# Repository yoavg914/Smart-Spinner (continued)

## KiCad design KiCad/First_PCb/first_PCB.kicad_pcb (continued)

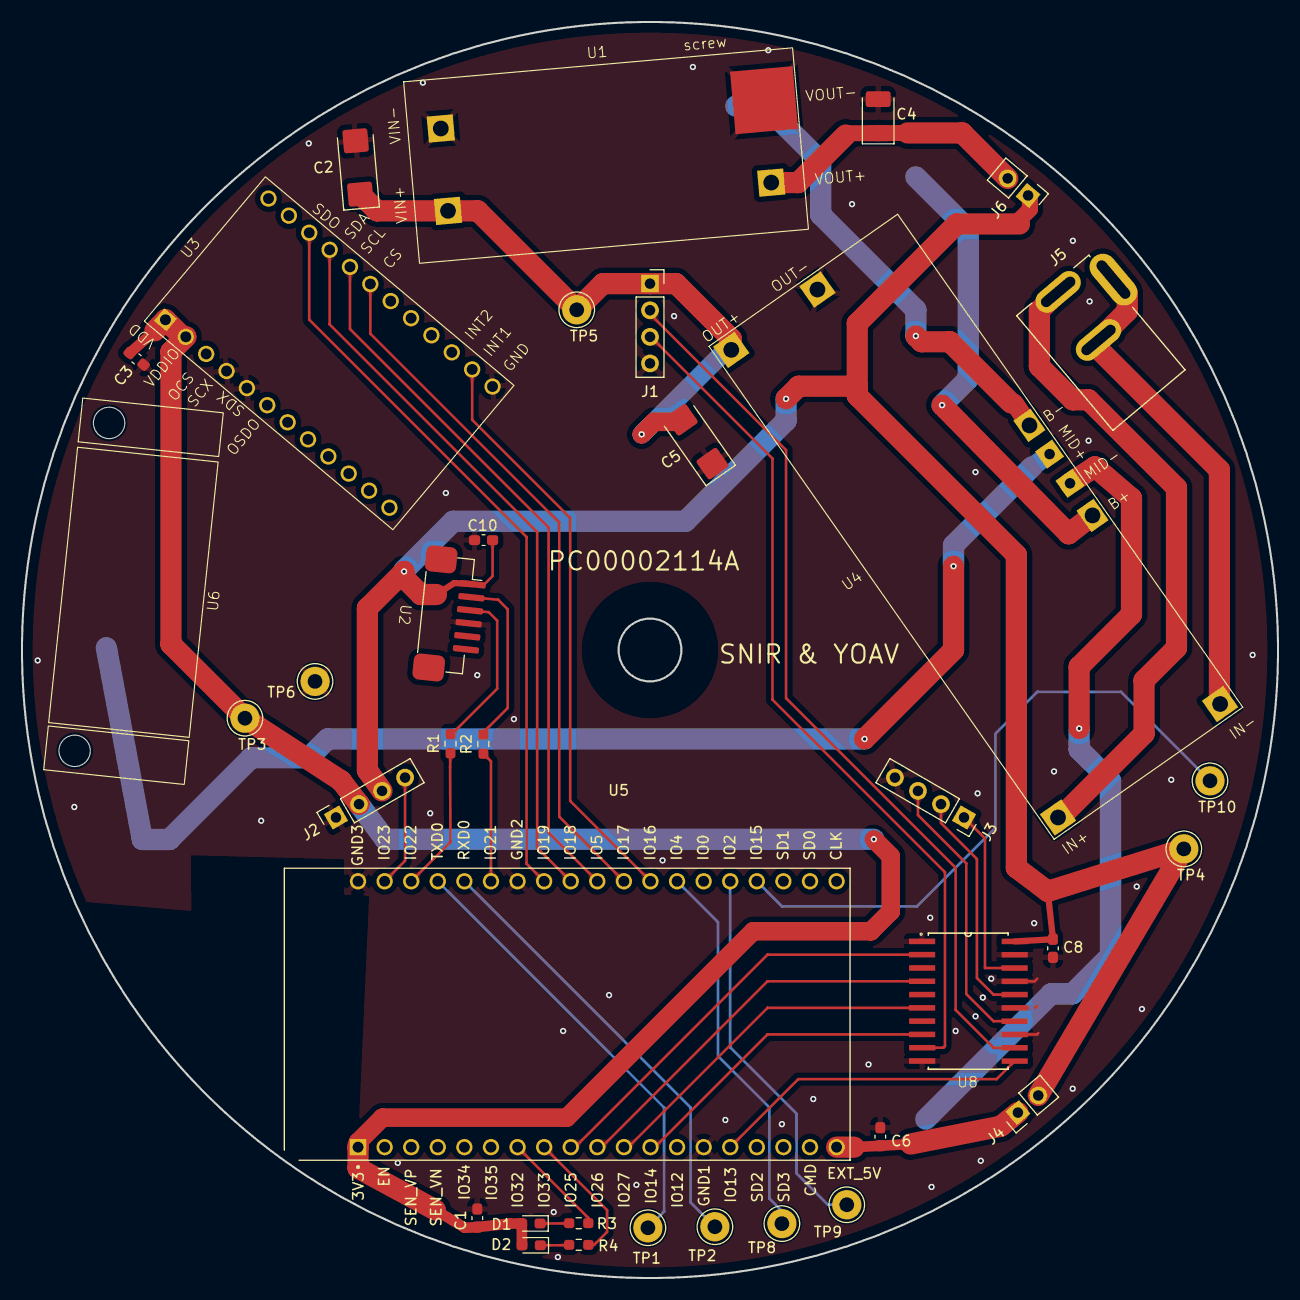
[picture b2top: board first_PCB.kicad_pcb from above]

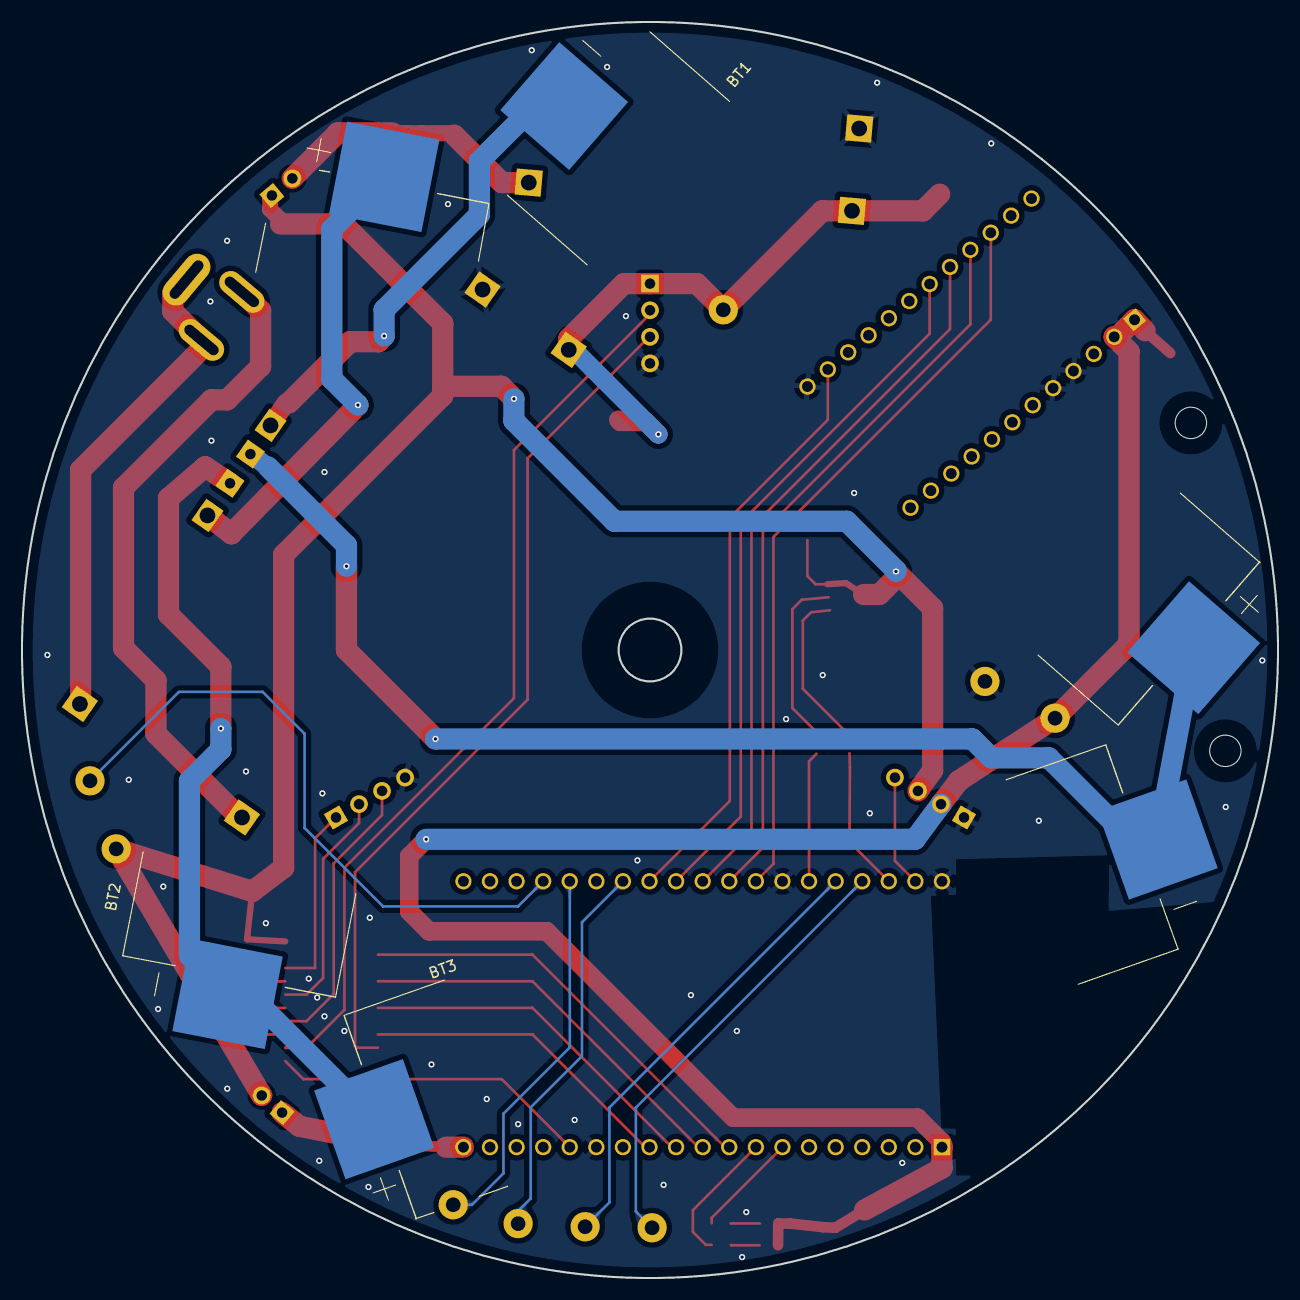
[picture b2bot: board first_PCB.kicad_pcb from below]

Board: 2 copper layers, 120.0 x 120.0 mm, 39 parts (3 on the bottom side), 41 nets.

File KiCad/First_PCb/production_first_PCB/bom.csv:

Designator,Footprint,Quantity,Value,LCSC Part #
"BT1, BT2, BT3",battery_holder,3,Battery Holder,
"C1, C10, C3, C6, C8",0603,5,10u,
"C2, C5",CP_EIA-6032-28_Kemet-C_HandSolder,2,47u,
C4,CP_EIA-3528-12_Kemet-T_HandSolder,1,47u,
D1,0603,1,red_LED,
D2,0603,1,green_LED,
"J1, J2, J3",PinSocket_1x04_P2.54mm_Vertical,3,Conn_01x04_Socket,
"J4, J6",PinHeader_1x02_P2.54mm_Vertical,2,Conn_01x02_Pin,
J5,NINIGI_DC-005,1,DC-005,
"R1, R2",0603,2,10,
"R3, R4",0603,2,250,
"TP1, TP10, TP2, TP3, TP4, TP5, TP6, TP8, TP9",TestPoint_Loop_D2.60mm_Drill1.4mm_Beaded,9,TestPoint,
U1,MT3608_no_conn_TH,1,MT3608 - No Connector,
U2,JST_GH125,1,GH1.25,
U3,STEVAL-MKI239A,1,STEVAL-MKI239A,
U4,PWR_SPLY12V_TH,1,EGBO UPS,
U5,MODULE_ESP32-DEVKITC-32D-TH,1,ESP32-DEVKITC-32D,
U6,TF_LUNA_mechanics,1,TF_LUNA_mechanics,
U8,74HCT244D-SOIC20,1,74HCT244D,

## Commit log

2025-07-06 Create REAME.txt
    in KICad
2025-07-06 added KICad files
    First Versions
2025-07-11 Create First PCB
2025-07-11 First arrengement - after conversiation with Boaz
2025-12-22 added all the kicad files & gerbers of the first pcb
2025-12-22 adding footprints and schematic symbols libraries
2025-12-22 added all the kicad files and gerbers of the second pcb
    after sending to manufacture.
2026-01-08 added production files
    BOM & Netlist
2026-01-08 added production files - Second PCB
    BOM & Netlist
2026-01-08 assembly and fab files
    - for soldering irena - first pcb
2026-01-08 assembly layout and BOM files
    for assembly and soldering
2026-06-13 Upload full PlatformIO project to esp_code/
